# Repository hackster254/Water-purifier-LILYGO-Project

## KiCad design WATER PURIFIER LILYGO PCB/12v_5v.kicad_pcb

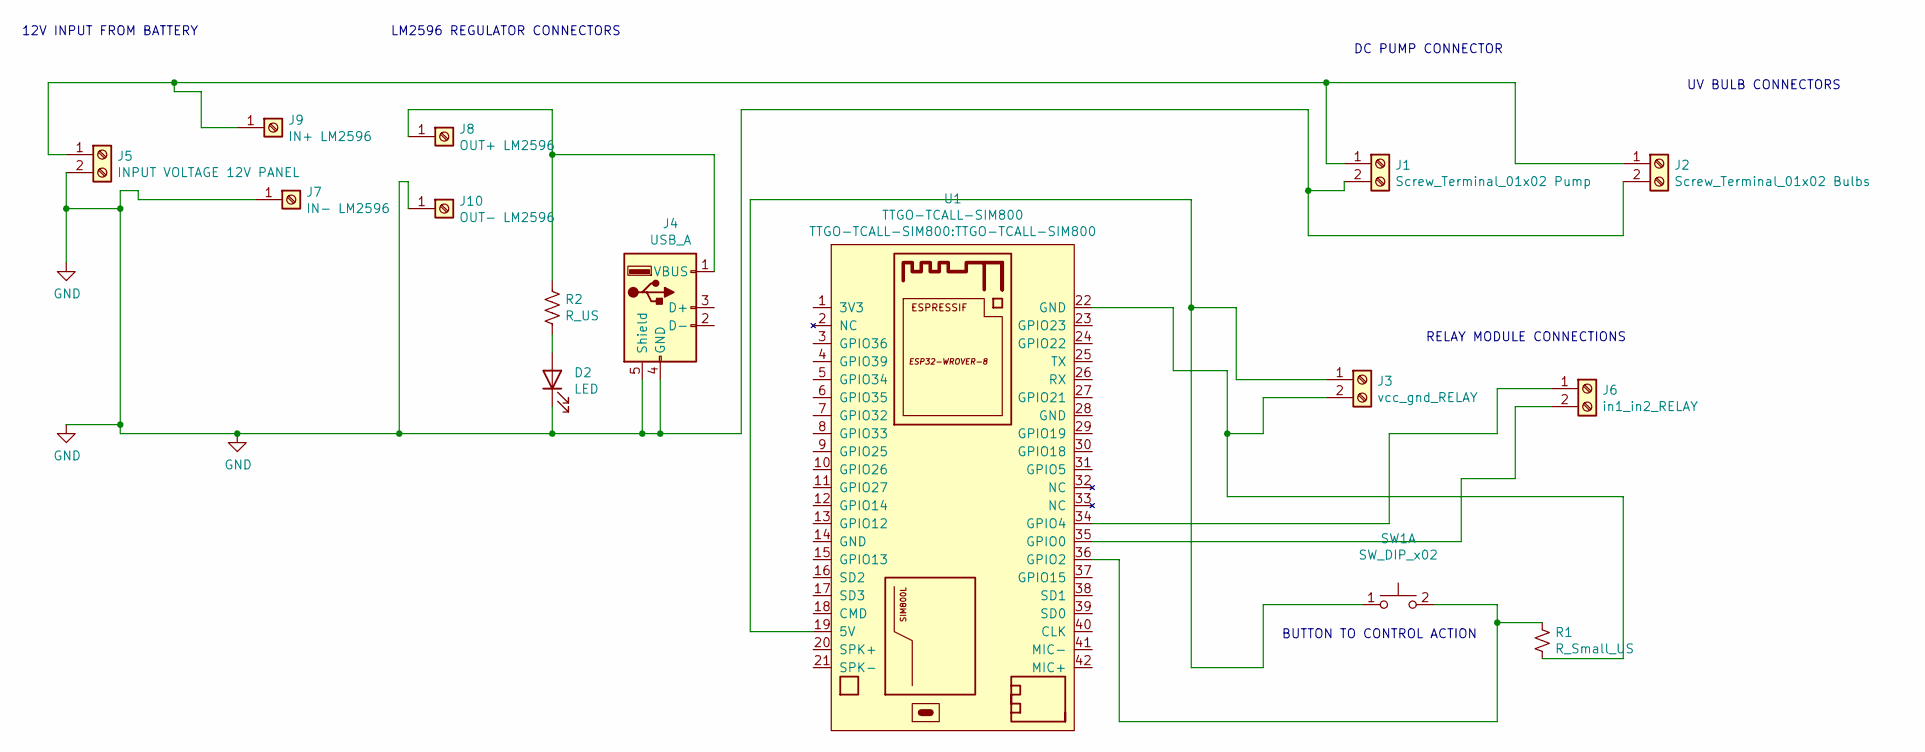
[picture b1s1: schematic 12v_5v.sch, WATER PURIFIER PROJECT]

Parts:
D2: LED; LED_D5.0mm
J1: Screw_Terminal_01x02 Pump; TerminalBlock_Altech_AK300-2_P5.00mm
J2: Screw_Terminal_01x02 Bulbs; TerminalBlock_Altech_AK300-2_P5.00mm
J3: vcc_gnd_RELAY; TerminalBlock_Altech_AK300-2_P5.00mm
J4: USB_A; USB_A_Molex_67643_Horizontal
J5: INPUT VOLTAGE 12V PANEL; TerminalBlock_Altech_AK300-2_P5.00mm
J6: in1_in2_RELAY; TerminalBlock_Altech_AK300-2_P5.00mm
J7: IN- LM2596; PinHeader_1x01_P1.00mm_Vertical
J8: OUT+ LM2596; PinHeader_1x01_P1.00mm_Vertical
J9: IN+ LM2596; PinHeader_1x01_P1.00mm_Vertical
J10: OUT- LM2596; PinHeader_1x01_P1.00mm_Vertical
R1: R_Small_US; R_Axial_DIN0204_L3.6mm_D1.6mm_P5.08mm_Horizontal
R2: R_US; R_Axial_DIN0204_L3.6mm_D1.6mm_P5.08mm_Horizontal
SW1: SW_DIP_x02; SW_PUSH_6mm_H5mm
U1: TTGO-TCALL-SIM800

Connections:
GND: D2.1 (K), J1.2, J2.2, J4.4 (GND), J4.5 (Shield), J5.2, J7.1, J10.1
unnamed: D2.2 (A), R2.2
unnamed: J1.1, J2.1, J5.1, J9.1
unnamed: J3.1, SW1.1 (C), U1.19 (5V)
unnamed: J3.2, R1.2, U1.22 (GND)
unnamed: J4.1 (VBUS), J8.1, R2.1
unnamed: J6.1, U1.34 (GPIO4)
unnamed: J6.2, U1.35 (GPIO0)
unnamed: R1.1, SW1.2 (D), U1.36 (GPIO2)

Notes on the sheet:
RELAY MODULE CONNECTIONS
UV BULB CONNECTORS
DC PUMP CONNECTOR
12V INPUT FROM BATTERY
BUTTON TO CONTROL ACTION
LM2596 REGULATOR CONNECTORS

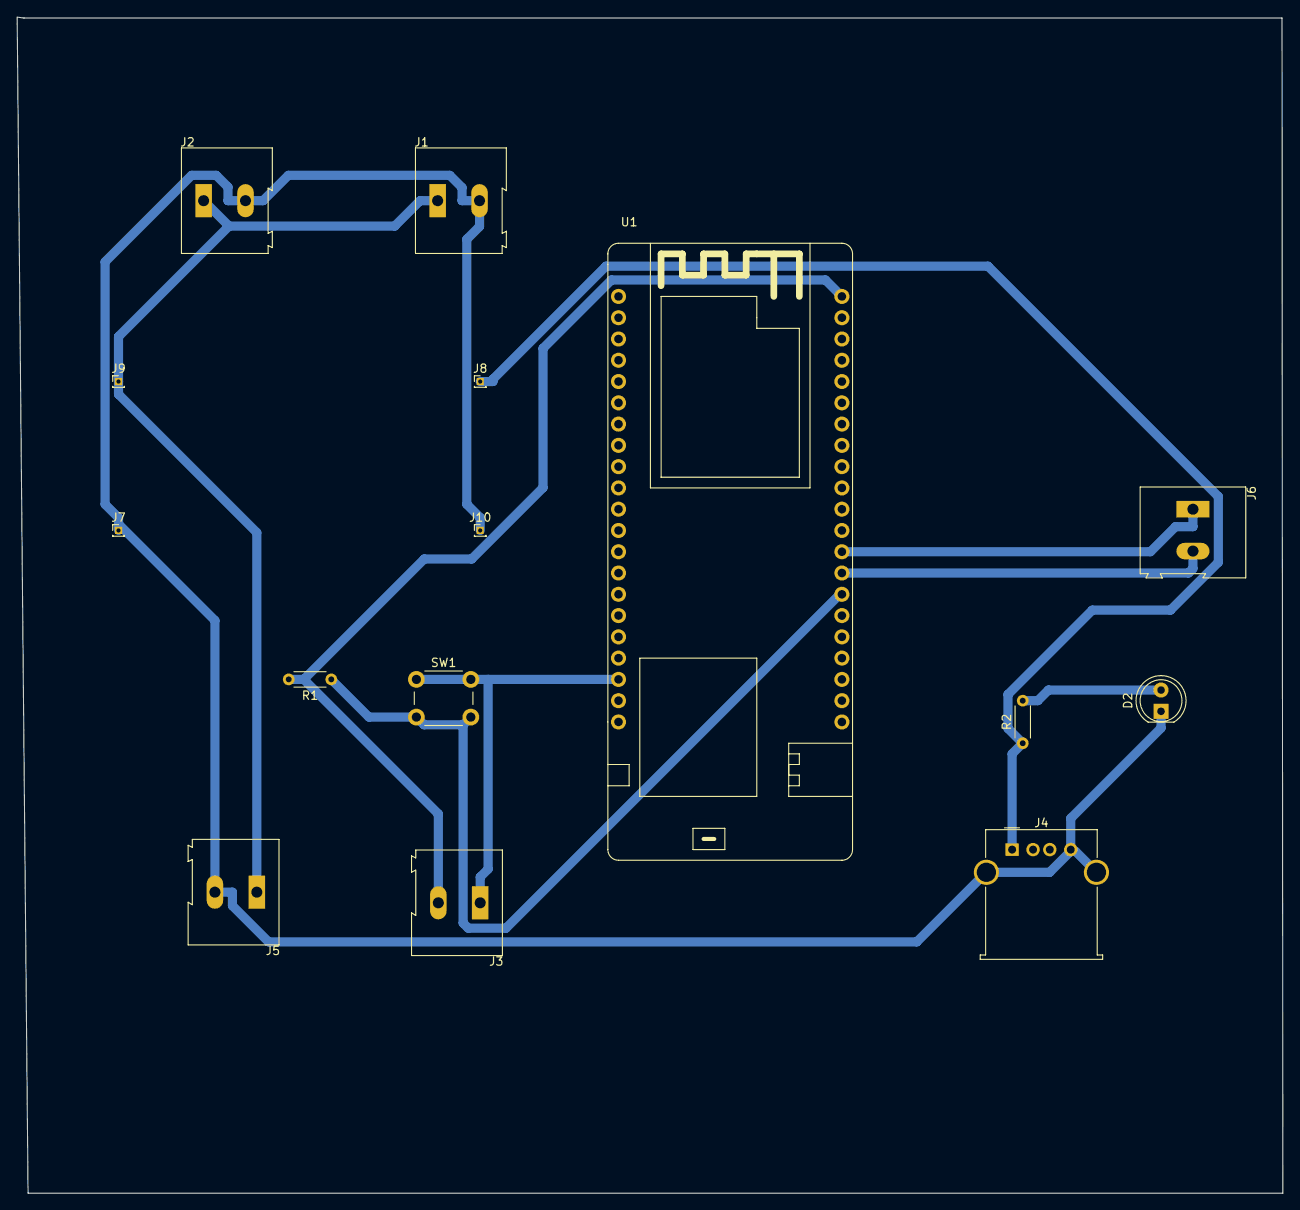
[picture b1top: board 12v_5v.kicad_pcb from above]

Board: 2 copper layers, 151.1 x 140.4 mm, 15 parts (0 on the bottom side), 9 nets.

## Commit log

2021-11-19 Added PCB kicad schematics
2021-11-21 Lilygo arduino code
2021-11-28 Final project presentation slides
2021-11-28 Final Project Report
